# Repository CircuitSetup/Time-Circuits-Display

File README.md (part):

# Time Circuits Display

|  |

This [repository](https://github.com/CircuitSetup/Time-Circuits-Display) holds the most current firmware for CircuitSetup's wonderful [Time Circuits Display](https://circuitsetup.us/product/complete-time-circuits-display-kit/) ("TCD") kit, a reproduction of an iconic part of the Delorean Time Machine.

The kit is available [here](https://circuitsetup.us/product/complete-time-circuits-display-kit/). The metal version is very popular among Delorean owners who convert their vehicle into a Time Machine. A testament to its build quality and accuracy is further the fact that it is used in the **movie-based, official musicals on tour** (2024-2026), and that a sample is part of the experience in the **"OUTATIME" [Escape Room](https://www.universalorlando.com/web/en/us/things-to-do/entertainment/universals-great-movie-escape) in Orlando, Florida**. Namedropping aside, this TCD makes an excellent centerpiece of every movie props collection. It can be used stand-alone or in combination with several [peripherals](#peripherals), both in car and home setups.

[View the instructions for assembling your CircuitSetup TCD Kit](https://github.com/CircuitSetup/Time-Circuits-Display/wiki)

And don't be fooled by the looks, it got brains, too!

|  |
|:--:|
| Click to watch the video |

|  |
|:--:|
| Click to watch the video |

Features include

- Clock-related:
  - Time keeping for years 1-9999, accurately based on Julian and Gregorian [calendars](#calendar-system)
  - Support for time zones and automatic DST (Daylight Saving adjustment)
  - Time synchronization through Internet ([NTP&#10548;](https://en.wikipedia.org/wiki/Network_Time_Protocol)) or [GPS](#gps-receiver)
  - [World Clock mode](#world-clock-mode): Show current time in different time zones on *destination time* and/or *last time departed* displays
  - [Alarm function](#alarm): Daily alarms, with weekday selection as well as snooze and auto-snooze functions
  - [Count-down timer](#count-down-timer): Count down from up to 99 minutes
  - [Yearly/monthly reminder](#yearlymonthly-reminder): Get a yearly or monthly acoustic reminder
  - [Sound on the hour](#additional-custom-sounds)
  - Time can be [spoken out loud](#martys-time-announcement) by "Marty McFly"
- Movie-related:
  - Movie-accurate [Beep](#beep-on-the-second) sound every second (4 modes)
  - Movie-accurate [time travel](#time-travel) function
  - Configuration options to emulate nearly all variations of the TCD shown in the trilogy
  - ["Return from Time Travel"](#time-travel): Return to real present time easily
  - ["Time-cycling"](#time-cycling): Movie-accurate time travel times displayed in *destination time* and *last time departed* displays, and cycled in configurable interval
  - [Exhibition mode](#exhibition-mode): Show a fixed time in *Present Time* display instead of a running clock. Helpful for filming or museums.
- Network capabilities:
  - Advanced network-accessible [Config Portal](#the-config-portal) for setup (http://timecircuits.local)
  - [Wireless communication](#connecting-props-wirelessly-bttf-network-bttfn) with compatible props such as CircuitSetup's [Flux Capacitor](https://circuitsetup.us/product/flux-capacitor-light-sound-kit/) and [SID](https://circuitsetup.us/product/delorean-time-machine-status-indicator-display-sid/), as well as the [Dash Gauges](https://circuitsetup.us/product/delorean-time-machine-dash-gauge-control-board/), [VSR](https://vsr.out-a-ti.me) and modified [Futaba Remote Control](https://circuitsetup.us/product/futaba-remote-stanley-display-wireless-control-kit/), for synchronized Time Travel sequences, replaying movie scenes, mutual remote control, and more. No need for even more wires in your Delorean.
  - [Home Assistant](#home-assistant--mqtt) (MQTT) support for sending and displaying messages, remote controlling and more.
  - Easy [firmware updates](#firmware-installation--firmware-update) over-the-air. No need to send in stuff for firmware updates, it's the 2020s after all.
- [Night mode](#night-mode): Dim or switch off displays on schedule, manually or sensor-controlled. So you won't be blinded during night drives.
- Audio output through [line-out](#audio-output) for time travel sound, music and [user-added](#additional-custom-sounds) sound. Connect your TCD to your (car) stereo for high-quality stereo-sound. No more "time traveling" through a 2" speaker. (Requires Control Board 1.4.5 or later)
- [Music player](#the-music-player): Play your mp3 files located on SD card, through your (car) stereo if available. 
- [Keypad-controlled menu](#the-keypad-menu) for adjusting various settings and viewing status through the three displays
- Support for numerous [peripherals](#peripherals):
  - [Fake "power switch"](#fake-power-switch) (eg. a [TFC drive switch](https://tfc.out-a-ti.me))
  - [Speedometer](#speedometer) (eg. CircuitSetup's [speedo](https://circuitsetup.us/product/delorean-time-machine-speedometer-kit) with built-in GPS receiver)
  - [GPS receiver](#gps-receiver) for time synchronization and actual [speed](#gps-for-speed) to be displayed on speedo
  - [Rotary encoders](#rotary-encoder) for manual selection of speed to be displayed on speedo, and/or audio volume
  - External [Time Travel trigger](#external-time-travel-trigger), with optional delay
  - [Temperature/humidity sensor](#room-condition-mode-temperaturehumidity-sensor) for [Room Condition mode](#room-condition-mode-temperaturehumidity-sensor) [display temperature and humidity in *destination time* and *last time departed* displays] and for displaying temperature on speedo while idle
  - Multi-purpose output for signaling/controlling other props [connected by wire](#connecting-props-by-wire) (for example flux lights, third party props)
- &#128007; &#129370; &#129370; &#129370; &#129370; &#129370; &#129370; &#129370; &#129370; &#129370; &#129370; &#129370; &#129370;

>[The A10001986 repository](https://tcd.out-a%2dti.me) is the upstream source for CircuitSetup's firmware releases. The [A10001986 edition](https://tcd.out%2da-ti.me) uses a slightly different sound-pack compared to the CircuitSetup edition, otherwise there are no differences between A10001986 and CircuitSetup releases of the same version.

For information on updating the firmware of your TCD, see [here](#firmware-installation--firmware-update).

#### What's new in version 4.00?

- GPS speed logic change: "Display GPS speed" and "Provide GPS speed to BTTFN clients" Config Portal options are gone. User can now switch between _Evaluate GPS speed_ and _Do not evaluate GPS Speed_ on-the-fly through keypad command ```8```. This toggles between (a) displaying GPS speed on speedo as well as sending it to BTTFN clients, and (b) using a rotary encoder, displaying "0", temperature, or switching the speedo off, depending on hardware configuration and other option settings.
- If GPS does not have a fix, the speedo will display "-" permanently (and no longer switch to "0" after a while). To avoid this, issue keypad command ```8``` to switch away from GPS speed.
- The former GPS speed "Update rate" selector is now labeled "GPS speed" and got a "disabled" option item which allows categorically disable GPS speed (which should be done in case of a permanently stationary installation to avoid polling the GPS receiver unnecessarily frequently).
- GPS: Keypad commands ```950```/```951``` disable/enable the GPS fix indicator in the present time's year field. Defaults to on.
- GPS: Keypad menu now has an item that shows if a GPS receiver has been detected during boot.
- Fix for undetected GPS receivers on very long cables.
- Re-arrange WiFi Configuration page for a better user experience
- Remap "show weekday of current present time's date" keypad command to more handy ```3``` (instead of rather unintuitive 39).
- Keypad command ```1971159357```, when entered twice, resets all settings to factory defaults.
- Sound-pack uploads are done through the _top_ file selector on the "Update & Upload" page, and no longer through the bottom one. The bottom one is for custom mp3 file upload only.
- **Future firmware updates may only consist of one single file instead of "main firmware" plus "sound-pack". Firmware updates will require an SD card. In order to update to versions beyond 4.00, version 4.00 must be installed first.**

## Initial Configuration

**Some key features of your TCD require an SD card.** The first step is therefore to put a **good-quality** ("endurance", "industrial", "long life", ...) **and empty microSD card into the card slot** on the back of the keypad. The SD card must be inserted before powering up the TCD. It is not recognized if inserted while the TCD is running. Furthermore, do not remove the SD card while the TCD is powered.

>SD/SDHC/SDXC cards up to 32GB are supported. The card needs to be FAT32-formatted (not exFAT). Transcend, Sandisk Ultra and Industrial, Verbatim Premium and Samsung Pro Endurance SDHC cards usually work fine. Some SD cards might not be recognized due to off-specs initialization quirks. SDUC cards are not supported.

The second step is to establish access to the TCD's configuration website ("Config Portal") in order to configure your TCD:

- Power up the TCD and wait until it shows a time (which is probably wrong).
- Connect your computer or handheld device to the WiFi network "TCD-AP".
- Navigate your browser to http://timecircuits.local or http://192.168.4.1 to enter the Config Portal.

#### Time zone and Time

The next step is to set the time zone. If the time zone isn't properly configured, the TCD will show a wrong time and DST (daylight saving) will not be switched on/off correctly.

- Click on "Settings" on the Config Portal's main page,
- specify your [time zone](#-time-zone), and
- click "SAVE".

The TCD will reboot. Afterwards, please re-connect your computer/handheld to "TCD-AP" and re-enter the Config Portal as described above.

Setting actual time:
- If the TCD is going to be connected to a WiFi network with internet access as described below, it will receive time information through NTP (network time protocol). No user interaction is required.
- Otherwise please set your local time through the [keypad menu](#how-to-set-the-real-time-clock-rtc).

#### Sound-pack re-installation (Firmware 3.23 an onwards)

If your factory-fresh TCD came with firmware version 3.23 or later, but no SD card, the next step is to re-install the sound-pack. The reason for this is that the sound-pack does not entirely fit into the device's flash memory and parts of it need to be installed on your SD card. Please see [here](#sound-pack-installation) for instructions.

The firmware version is displayed in the footer of the Config Portal's main menu page.

#### WiFi Setup

The TCD knows two ways of WiFi operation: Either it creates its own WiFi network or it connects to a pre-existing WiFi network.

As long as the device is unconfigured, it creates a WiFi network of its own named "TCD-AP". This is called **"Access point mode"** or **"AP-mode"**. In this mode, other WiFi devices - such as other props or a computer - can connect to the TCD, but the TCD can't access the internet (and therefore not synchronize time through NTP). Also, [HA/MQTT](#home-assistant--mqtt) is not possible.

It is ok to leave the TCD in this mode if there is no WiFi network available.

<details>
<summary>More...</summary>

>Please do not leave computers/handhelds permanently connected to the TCD's AP. These devices might think they are connected to the internet and therefore hammer the TCD with DNS and HTTP requests which might lead to packet loss and disruptions.

>If you want your device to remain in AP-mode, please choose a suitable WiFi channel on the Config Portal's "WiFi Configuration" page. See [here](#-wifi-channel).

</details>

In a typical **home setup**, however, you might want to connect the TCD to your local WiFi network. This allows for for time synchronization (NTP) and [HA/MQTT](#home-assistant--mqtt):

To connect your TCD to your WiFi network, navigate to the Config Portal and click on "WiFi Configuration". The bare minimum is to select an WiFi network name (SSID) and a WiFi password.

<details>
<summary>More...</summary>
  
>If there are several access points (AP) with identical SSID nearby, the TCD will connect to the first one found which might not be the nearest/strongest. It is therefore recommended to select a specific AP by its BSSID (AP's MAC address). You can either manually find out your AP's BSSID and enter it or have it filled out automatically: Click "Scan for networks", then "Show all APs". If you click on an AP in the list, its BSSID will be copied into BSSID field in the form below. To see which AP is which, hover over the name to see its BSSID as a tooltip.

>The TCD requests an IP address via DHCP, unless you entered valid data in the fields for static IP addresses (IP, gateway, netmask, DNS). If the device is inaccessible as a result of incorrect static IPs, hold ```ENTER``` while powering it up until the white LED lights up; static IP data will be deleted and the device will return to using DHCP.
</details>

After saving the WiFi configuration settings, the TCD reboots and tries to connect to your selected WiFi network. If that fails, it will again start in access point mode.

If your TCD is **mounted in a car**, there is a special Car Mode that allows having a WiFi network configured (for administrative purposes and NTP time synchronization) and switching between AP-Mode and WiFi-connection through keypad commands. See [here](#car-mode) and [here](#car-setup---best-practice). So, despite using your TCD in a car, you can at this point configure a WiFi Connection, eg. to your cell phone's hotspot, and then put the TCD into Car Mode which reboots it into Access-Point mode.

After completing these steps, your TCD is ready for use; you can also continue configuring it to your personal preferences through the Config Portal.

## The Config Portal

The "Config Portal" is the TCD's configuration website. 

|  |
|:--:| 
| *The Config Portal's main page* |

It can be accessed as follows:

#### If TCD is in AP mode

- Connect your computer or handheld device to the WiFi network "TCD-AP".
- Navigate your browser to http://timecircuits.local or http://192.168.4.1 to enter the Config Portal.
- (For proper operation, please disconnect your computer or handheld from TCD-AP when you are done with configuring your TCD. These devices can cause high network traffic, resulting in severe performance penalties.)

#### If TCD is connected to WiFi network

- Connect your handheld/computer to the same WiFi network to which the TCD is connected, and
- navigate your browser to http://timecircuits.local

  <details>
  <summary>More...</summary>

  >Accessing the Config Portal through this address requires the operating system of your handheld/computer to support Bonjour/mDNS: Windows 10 version TH2     (1511) [other sources say 1703] and later, Android 13 and later; MacOS and iOS since the dawn of time.

  >If connecting to http://timecircuits.local fails due to a name resolution error, you need to find out the TCD's IP address: Hold ```ENTER``` on the TCD's keypad for 2 seconds, then repeatedly  press 8 until "NETWORK" is shown, then press ```5```. The TCD will show its current IP address. Then, on your handheld or computer, navigate to http://a.b.c.d (a.b.c.d being the IP address as shown on the display) in order to enter the Config Portal.
</details>

In the main menu, click on "Settings" or "Peripherals" to configure your TCD. 

|  |
|:--:| 
| *Click for full screenshot* |

A full reference of the Config Portal is [here](#appendix-a-the-config-portal).

## Basic Operation

*Present time* is a clock and normally shows actual local present time, as received from the network or set up through the [keypad menu](#how-to-set-the-real-time-clock-rtc).

*Destination time* and *Last time departed* are stale. These, by default, work like in the movie: Upon a time travel, *present time* becomes *last time departed*, and *destination time* becomes *present time*. Or in Doc's words: The red one tells you where you're going. The green one tells you where you are. The yellow one tells you where you were.

The keypad is for programming destination times like in the movies and for controlling the TCD through commands. "Keypad commands" are numerical codes to be typed on the digit keys followed by ```ENTER```. ```ENTER``` is the button right above the "Clear" badge.

<details>
<summary>"REPLACE BATTERY" displayed on boot?</summary>
If "REPLACE BATTERY" is shown upon boot, the onboard CR2032 battery is depleted and needs to be replaced. For technical reasons, "REPLACE BATTERY" will also show up the very first time you power-up the TCD *after* changing the battery. You can, of course, disregard that message at that point.
</details>

### Powering down the TCD

The TCD sometimes writes data to either the internal flash memory or the SD card. These write operations should not be interrupted by a power loss.

In general, it is safe to power-down the TCD after it has been [fake-powered-down](#fake-power-switch) or when it has been idle for 15 seconds. Try to avoid powering down the TCD
- when it is clearly busy (such as when copying or renaming audio files);
- within 15 seconds after changing the display mode (World Clock, Room condition, geolocation, …) or audio volume through a Rotary Encoder, 
- if [**_Make time travel persistent_**](#persistent--non-persistent-time-travels) is checked: in the first few seconds after a timetravel.

### Calendar system

The TCD firmware uses the [Julian Calendar&#10548;](https://en.wikipedia.org/wiki/Julian_calendar) from Jan 1, 1, until Sep 2, 1752, and for later dates the [Gregorian&#10548;](https://en.wikipedia.org/wiki/Gregorian_calendar) one. Sep 2, 1752, was the last day the Julian calendar was used in the ["First" British Empire&#10548;](https://en.wikipedia.org/wiki/British_Empire#%22First%22_British_Empire_(1707%E2%80%931783)) (Great Britain and its colonies, including eastern parts of North America, Canada). Other countries stopped using this calendar system way earlier; most of Europe, including Spain and its colonies worldwide, had switched in 1582 already.

Since the time machine was built in the USA, my guess is Doc would have picked 1752. (One might argue that California was a Spanish colony, but it only became that in 1769.)

So, what does this mean? First off, in the Julian calendar every 4th year is a leap year; in the Gregorian calendar there are some exceptions to this rule. As a result, the two calendars were drifting apart over time, and dates didn't match. As of 2023, the Julian calendar is 13 days ahead.

Secondly, and as a result of this drift, when countries switched from one to the other calendar system, days were skipped. In case of the switch in 1752, Sep 3 until Sep 13 were skipped, so after Sep 2 came Sep 14. For using the TCD this means that dates entered within that skipped period are corrected to Sep 14.

Neither the Gregorian nor the Julian Calendar know a "year 0"; 1AD followed after 1BC. Nevertheless, it is possible to travel to year 0. In good old Hollywood tradition, I won't let facts stand in the way of an authentic movie experience.

### Time-cycling

"Time cycling" is a decorative mode of operation in which the device cycles through a list of pre-programmed *destination* and *last time departed* times. These pre-programmed times match the dates/times of all time-travels that take place in the three movies.

Time-cycling is enabled by setting up a **_Time-cycling Interval_** in the Config Portal or the [keypad menu](#how-to-select-the-time-cycling-interval). The device will then cycle through named list every 5th, 10th, 15th, 30th or 60th minute. The option **_Animate time-cycling_** decides whether the times simply switch or the cycling event looks like someone entered a new destination date.

Triggering a time-travel pauses time-cycling for 30 minutes.

### World Clock mode

In World Clock (WC) mode, the red and yellow displays show not some stale times, but current time in other time zones. These time zones can be configured in Config Portal. At least one time zone (for either the red or yellow display) must be configured in order to use WC mode. Optionally, also names for cities/locations for these time zones can be entered in the Config Portal and shown [instead of the date or alternately](#world-clock-mode-1). Names can only contain letters a-z, numbers 0-9, space and minus. 

|  |
|:--:|
| Click to watch the video |

|  |
|:--:|
| *World Clock mode* |

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
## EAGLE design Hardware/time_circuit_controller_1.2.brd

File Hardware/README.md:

# PCB Revision History
## Control Board
v1.4.5 (8/1/24)
- Consolodated inputs/outputs into 8 pin screw connector
- Added label for TFC connections
- Added ground to audio line output screw connector
- Moved reset and io0 buttons to back of the board
- Added ability to switch between line out and speaker audio

v1.4 (7/1/24)
- Added dedicated audio line out
- Switched to original style TRW enter button
- Added on-board ESP32 module
- Added 3.3V power supply
- Added serial USB chip with ESD filtering
- Added micro-USB connector to back of board
- Moved RTC battery to rear of the PCB for ease of changing
- Changed volume pot to rear facing
- Moved micro-SD card to the rear of the board, and swtiched to a flip out holder
- 3d printed lens holder is now screwed to the PCB
- Changed Speedo and I2C to 2.54mm screw connectors
- Removed PCF2129AT and extra caps footprints
- Changed to TRW style mounting holes (3)

v1.3 (7/1/22)
- Added switch for lens LEDs
- Added header for TT In (GPIO 27)
- Added reverse polarity protection for power connectors
- Split resistors for keypad LEDs to make it so green LED can be brighter
- Added labels for PWR Trigger, TT Out, TT In, and Speedo

v1.2 (6/1/21)
- Fixed footprint for enter button
- Added 5.0V/3.3V level shifter, and ESD protection for I2C lines. This will prevent random glitches in I2C, and keep the ESP32 happy.
- Added footprint for PCF2129AT RTC in case DS3231 becomes unavailable or too expensive. Both should not be populated at the same time.
- Changed volume to connect to GPIO32 on ESP32 instead of amp GAIN_SLOT
- Updated schematic to include some notes

[OctoPart BOM](https://octopart.com/bom-tool/zCnlEeUa)

## Time Circuits Display
v1.31
- Made mounting holes slightly larger
- Moved some traces so they are not as close to pins

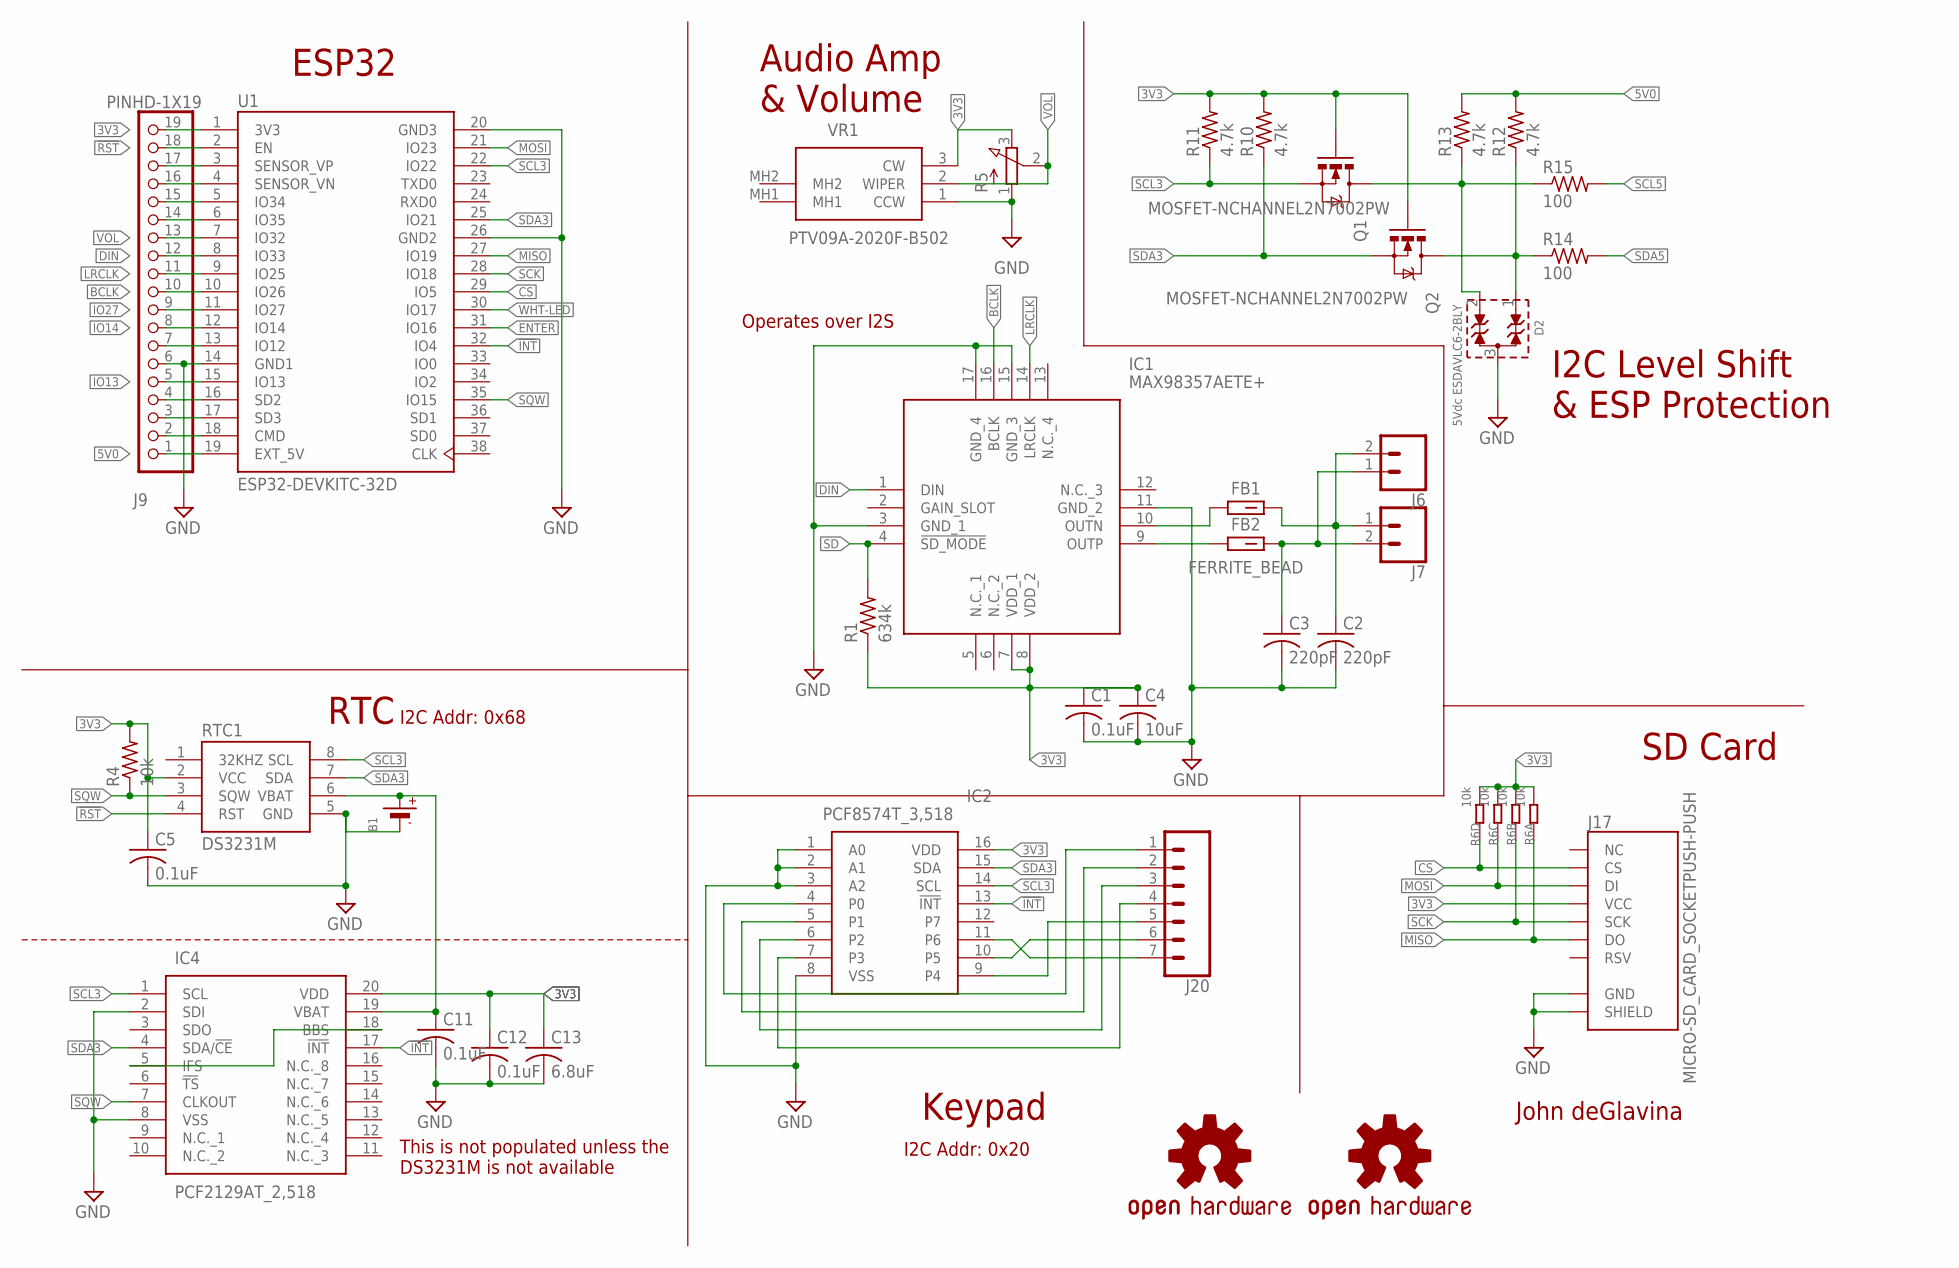
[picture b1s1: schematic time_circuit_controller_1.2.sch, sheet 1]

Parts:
B1: BATTERYCR2032_BAT-HLD-001; CR2032_SMT_BAT-HLD-001
C1, C5, C11, C12: 0.1uF; C0603
C2, C3: 220pF; C0603
C4: 10uF; C0603
C13: 6.8uF; C0603
D2: 5Vdc ESDAVLC6-2BLY; WE-TVS_SOT23-3L
FB1, FB2: FERRITE_BEAD; BEADC1608X95N
IC1: MAX98357AETE+; QFN50P300X300X80-17N
IC2: PCF8574T_3,518; SOIC127P1032X265-16N
IC4: PCF2129AT_2,518; SOIC127P1032X265-20N
J6: CONN_02-JST-2MM-SMT; JST-2-SMD
J7: CONN_02; 1X02
J9: PINHD-1X19; 1X19
J17: MICRO-SD_CARD_SOCKETPUSH-PUSH; MICRO-SD-SOCKET
J20: CONN_07LOCK; 1X07_LOCK
LOGO1, LOGO2: OSHW-LOGOL; OSHW-LOGO-L
Q1, Q2: MOSFET-NCHANNEL2N7002PW; SOT323
R1: 634k; R0603
R4: 10k; R0603
R5: 3RP/1610N
R6: 10k; RA1206-8
R10, R11, R12, R13: 4.7k; R0603
R14, R15: 100; R0603
RTC1: DS3231M; SO08
U1: ESP32-DEVKITC-32D; MODULE_ESP32-DEVKITC-32D
VR1: PTV09A-2020F-B502; PTV09A2020FB502

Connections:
3V3: C1.1, C4.1, C5.1, C12.1, C13.1, IC1.7 (VDD_1), IC1.8 (VDD_2), IC2.16 (VDD), IC4.20 (VDD), J9.19, J17.VCC, Q1.1 (G), Q2.1 (G), R1.1, R4.2, R5.3 (E), R6.1, R6.2 (1), R6.3 (1), R6.4 (1), R10.2, R11.2, RTC1.2 (VCC), U1.1 (3V3), VR1.3 (CW); also elsewhere on the board
5V0: J9.1, R12.2, R13.2, U1.19 (EXT_5V); also elsewhere on the board
!INT: IC2.13 (!INT), IC4.17 (!INT), U1.32 (IO4)
!RST: J9.18, RTC1.4 (RST), U1.2 (EN); also elsewhere on the board
AGND: B1.-, C1.2, C2.2, C3.2, C4.2, C5.2, C11.2, C12.2, C13.2, D2.3 (GND), IC1.3 (GND_1), IC1.11 (GND_2), IC1.15 (GND_3), IC1.17 (GND_4), IC2.1 (A0), IC2.2 (A1), IC2.3 (A2), IC2.8 (VSS), IC4.2 (SDI), IC4.8 (VSS), J9.6, J17.CD1 (SHIELD), J17.GND, R5.1 (A), RTC1.5 (GND), U1.14 (GND1), U1.20 (GND3), U1.26 (GND2), VR1.1 (CCW); also elsewhere on the board
BCLK: IC1.16 (BCLK), J9.10, U1.10 (IO26)
CS: J17.CS, R6.5 (2), U1.29 (IO5)
DIN: IC1.1 (DIN), J9.12, U1.8 (IO33)
ENTER: U1.31 (IO16); also elsewhere on the board
IO13: J9.5, U1.15 (IO13); also elsewhere on the board
IO14: J9.8, U1.12 (IO14); also elsewhere on the board
IO27: J9.9, U1.11 (IO27)
LRCLK: IC1.14 (LRCLK), J9.11, U1.9 (IO25)
MISO: J17.DO, R6.8 (2), U1.27 (IO19); also elsewhere on the board
MOSI: J17.DI, R6.6 (2), U1.21 (IO23); also elsewhere on the board
unnamed: IC2.11 (P6), J20.7
unnamed: FB1.1, IC1.10 (OUTN)
unnamed: B1.+$1 (+), B1.+$2 (+), C11.1, IC4.19 (VBAT), RTC1.6 (VBAT)
unnamed: IC2.4 (P0), J20.1
unnamed: IC2.9 (P4), J20.5
unnamed: J9.15, U1.5 (IO34)
unnamed: IC4.5 (IFS), IC4.18 (BBS)
unnamed: FB2.1, IC1.9 (OUTP)
unnamed: IC2.5 (P1), J20.2
unnamed: IC2.6 (P2), J20.3
unnamed: IC2.7 (P3), J20.4
unnamed: J9.14, U1.6 (IO35)
unnamed: IC2.10 (P5), J20.6
unnamed: J9.16, U1.4 (SENSOR_VN)
unnamed: J9.17, U1.3 (SENSOR_VP)
unnamed: J9.7, U1.13 (IO12)
unnamed: J9.4, U1.16 (SD2)
unnamed: J9.3, U1.17 (SD3)
unnamed: J9.2, U1.18 (CMD)
OUTN: C2.1, FB1.2, J6.2 (1), J7.1
OUTP: C3.1, FB2.2, J6.1 (2), J7.2
SCK: J17.SCLK (SCK), R6.7 (2), U1.28 (IO18); also elsewhere on the board
SCL3: IC2.14 (SCL), IC4.1 (SCL), Q1.2 (S), R11.1, RTC1.8 (SCL), U1.22 (IO22)
SCL5: R15.2; also elsewhere on the board
SD: IC1.4 (!SD_MODE), R1.2
SDA3: IC2.15 (SDA), IC4.4 (SDA/!CE), Q2.2 (S), R10.1, RTC1.7 (SDA), U1.25 (IO21)
SDA5: R14.2; also elsewhere on the board
SQW: IC4.7 (CLKOUT), R4.1, RTC1.3 (SQW), U1.35 (IO15)
VOL: J9.13, R5.2 (S), U1.7 (IO32), VR1.2 (WIPER)
WHT-LED: U1.30 (IO17); also elsewhere on the board
_SCL5: D2.2 (I/O2), Q1.3 (D), R13.1, R15.1
_SDA5: D2.1 (I/O1), Q2.3 (D), R12.1, R14.1

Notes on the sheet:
RTC
Keypad
SD Card
ESP32
I2C Level Shift & ESP Protection
Audio Amp & Volume
John deGlavina
This is not populated unless the DS3231M is not available
I2C Addr: 0x68
Operates over I2S
I2C Addr: 0x20

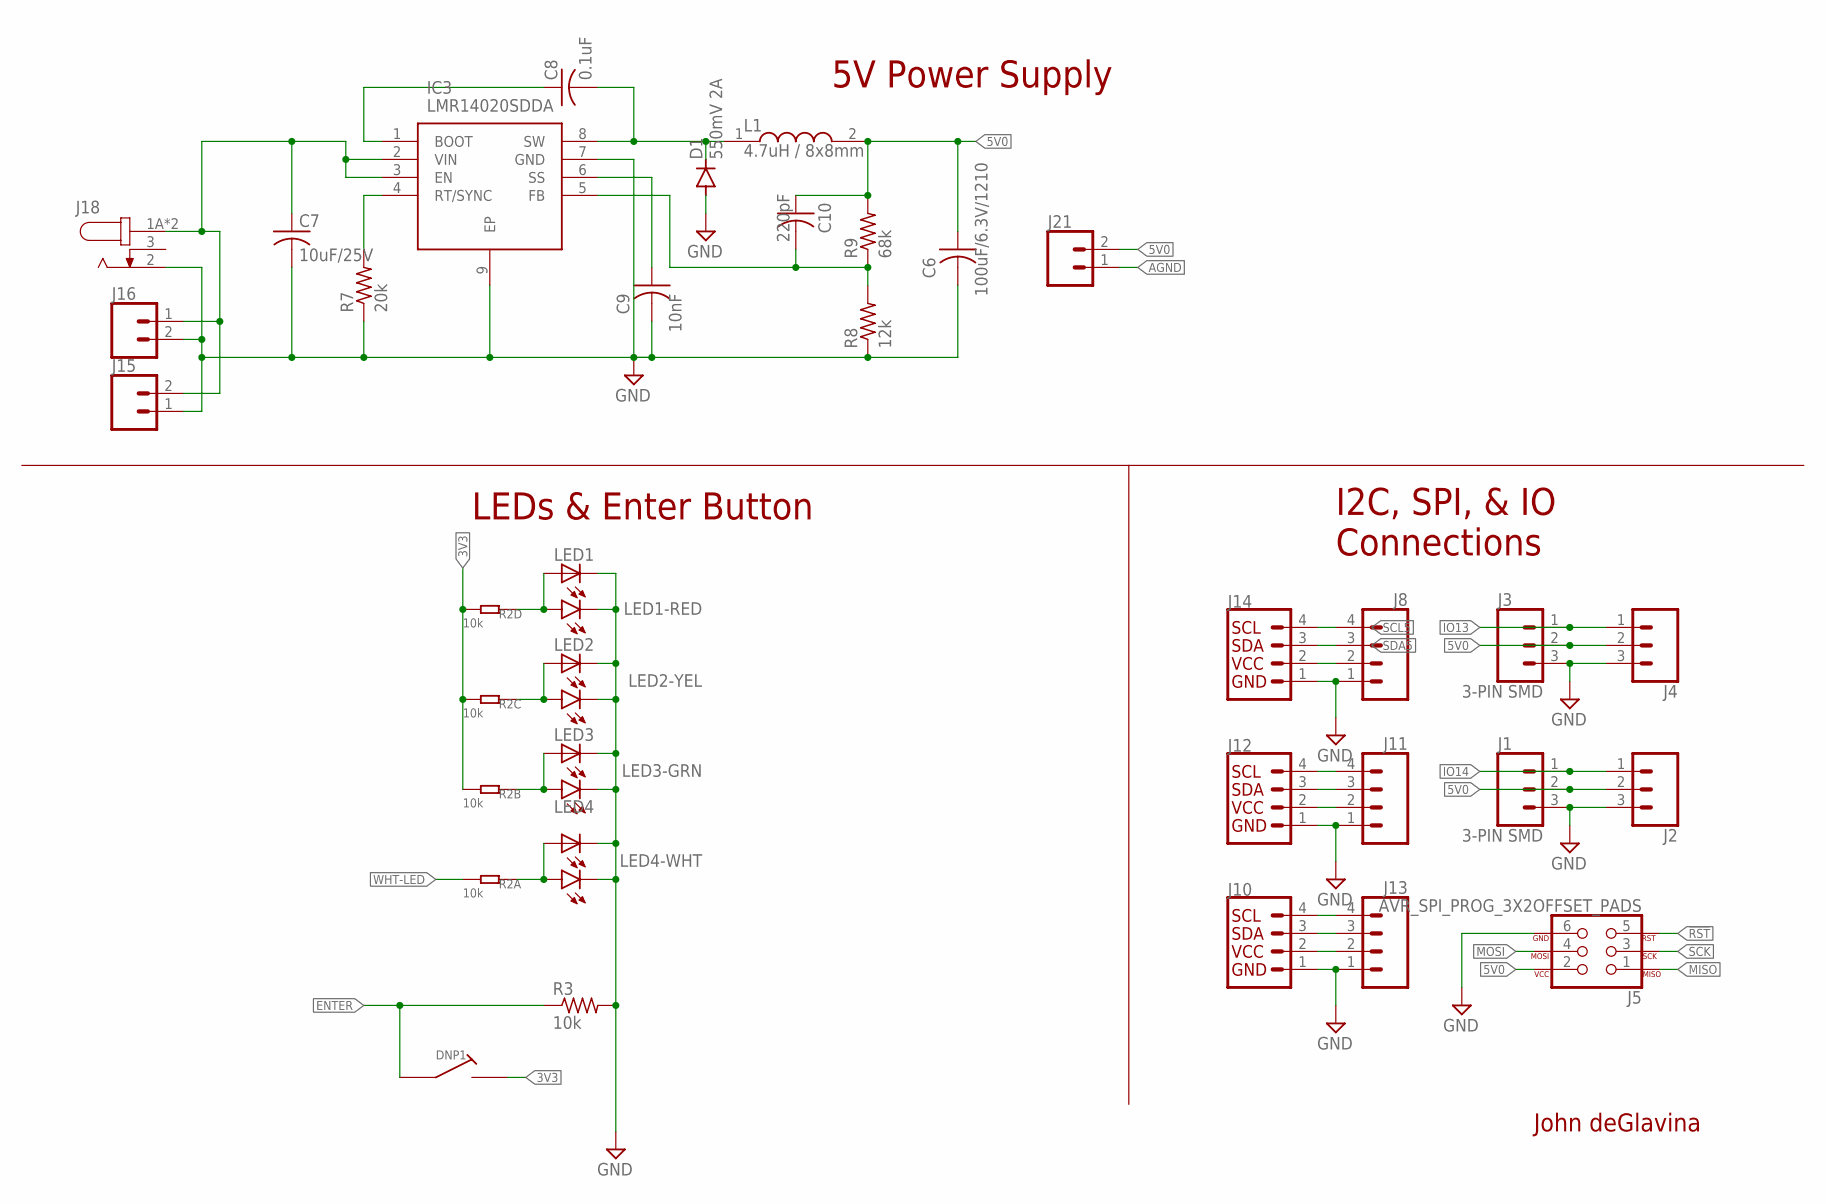
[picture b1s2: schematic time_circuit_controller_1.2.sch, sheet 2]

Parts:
C6: 100uF/6.3V/1210; C1210
C7: 10uF/25V; C0805
C8: 0.1uF; C0603
C9: 10nF; C0603
C10: 220pF; C0603
D1: 550mV 2A; DO214AC
DNP1: SWITCH-PINHEAD; PIN-1X2-3.5MM
IC3: LMR14020SDDA; SOIC127P600X170-9N
J1, J3: 3-PIN SMD; JST-3-SMD
J2, J4: CONN_03LOCK_LONGPADS; 1X03_LOCK_LONGPADS
J5: AVR_SPI_PROG_3X2OFFSET_PADS; 2X3_OFFSET
J8, J11, J13: CONN_04SMD_2.54; 1X04_5.5MM_STRAIGHT
J10, J12, J14: I2C_STANDARD; 1X04
J15, J21: CONN_023.5MM; SCREWTERMINAL-3.5MM-2
J16: CONN_02-JST-2MM-SMT; JST-2-SMD
J18: 9-12VAC; CUI_PJ-002AH-SMT-TR
L1: 4.7uH / 8x8mm; INDPM8082X300N
LED1, LED2, LED3, LED4: LEDCHIPLED_1206; CHIPLED_1206
LED1-RED, LED2-YEL, LED3-GRN, LED4-WHT: LED5MM
R2: 10k; RA1206-8
R3: 10k; R0603
R7: 20k; R0603
R8: 12k; R0603
R9: 68k; R0603

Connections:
3V3: DNP1.P$2 (2), R2.2 (1), R2.3 (1), R2.4 (1); also elsewhere on the board
5V0: C6.1, C10.1, J1.2, J2.2, J3.2, J4.2, J5.2, J8.2, J10.2, J11.2, J12.2, J13.2, J14.2, J21.2, L1.2, R9.2; also elsewhere on the board
!RST: J5.5; also elsewhere on the board
AGND: C6.2, C7.2, C9.2, D1.A, IC3.7 (GND), IC3.9 (EP), J1.3 (1), J2.3, J3.3 (1), J4.3, J5.6, J8.1, J10.1, J11.1, J12.1, J13.1, J14.1, J15.1, J16.2 (1), J18.2, J21.1, LED1.C, LED1-RED.K (C), LED2.C, LED2-YEL.K (C), LED3.C, LED3-GRN.K (C), LED4.C, LED4-WHT.K (C), R3.2, R7.1, R8.1; also elsewhere on the board
BOOT1: C8.1, IC3.1 (BOOT)
ENTER: DNP1.P$1 (1), R3.1; also elsewhere on the board
FB1: C10.2, IC3.5 (FB), R8.2, R9.1
IO13: J3.1 (3), J4.1; also elsewhere on the board
IO14: J1.1 (3), J2.1; also elsewhere on the board
MISO: J5.1; also elsewhere on the board
MOSI: J5.4; also elsewhere on the board
unnamed: LED1.A, LED1-RED.A, R2.5 (2)
unnamed: LED2.A, LED2-YEL.A, R2.6 (2)
unnamed: LED3.A, LED3-GRN.A, R2.7 (2)
unnamed: LED4.A, LED4-WHT.A, R2.8 (2)
RT1: IC3.4 (RT/SYNC), R7.2
SCK: J5.3; also elsewhere on the board
SCL5: J8.4, J10.4, J11.4, J12.4, J13.4, J14.4; also elsewhere on the board
SDA5: J8.3, J10.3, J11.3, J12.3, J13.3, J14.3; also elsewhere on the board
SS1: C9.1, IC3.6 (SS)
SW1: C8.2, D1.C, IC3.8 (SW), L1.1
VIN1: C7.1, IC3.2 (VIN), IC3.3 (EN), J15.2, J16.1 (2), J18.1A (1), J18.1B (1)
WHT-LED: R2.1; also elsewhere on the board

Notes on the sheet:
5V Power Supply
LEDs & Enter Button
I2C, SPI, & IO Connections
John deGlavina

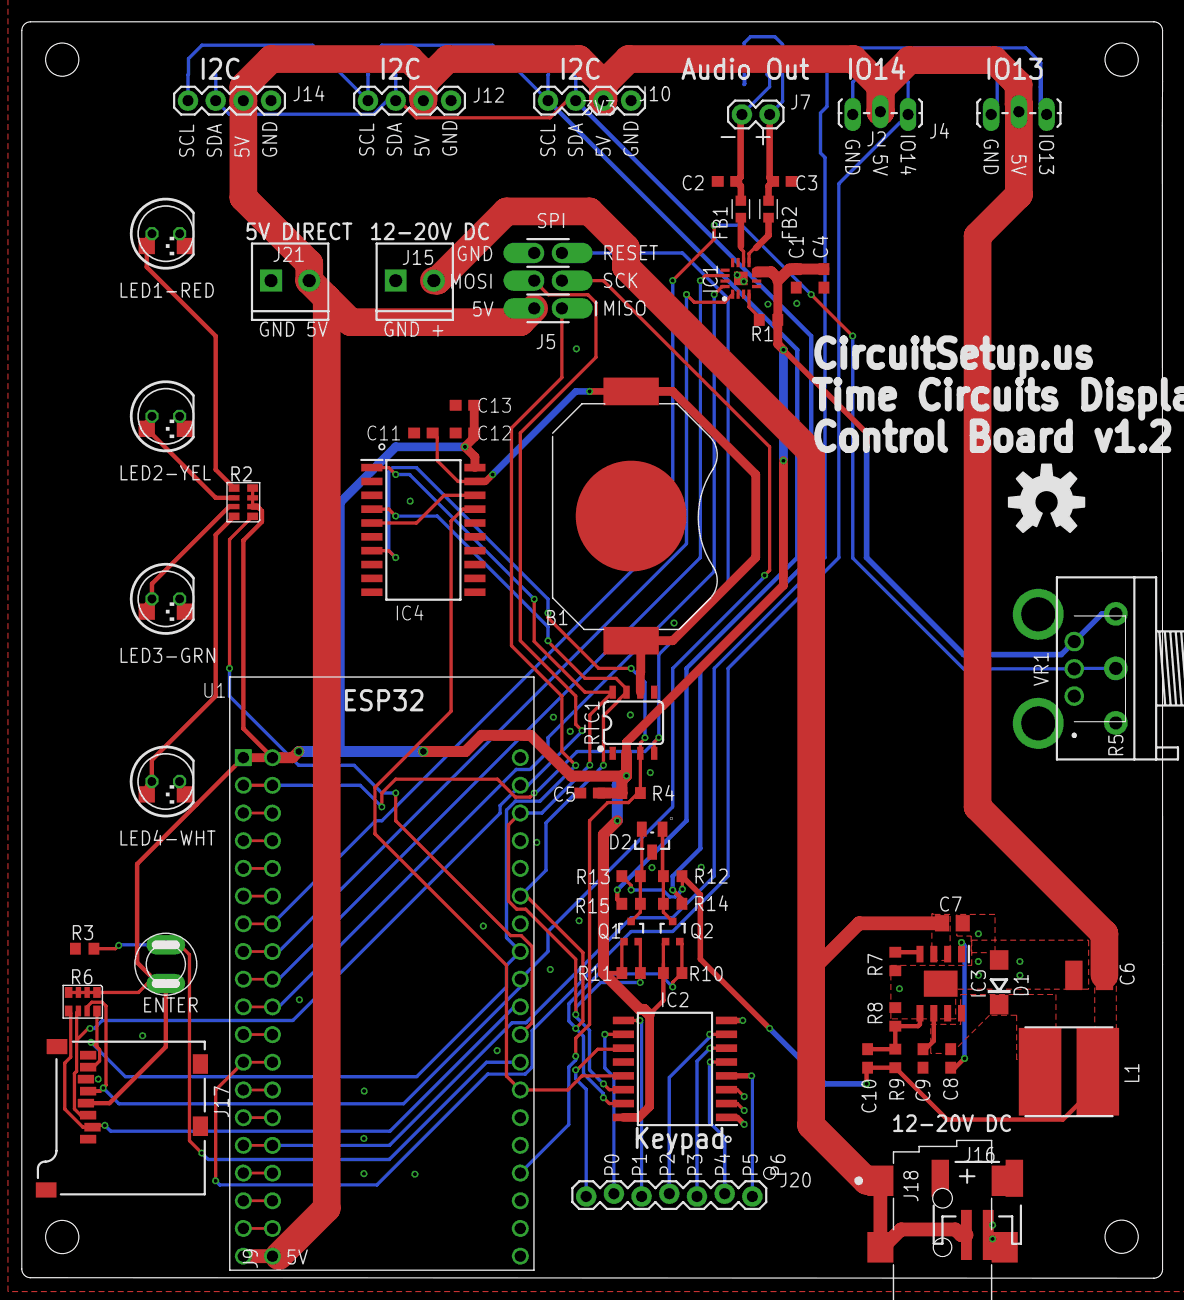
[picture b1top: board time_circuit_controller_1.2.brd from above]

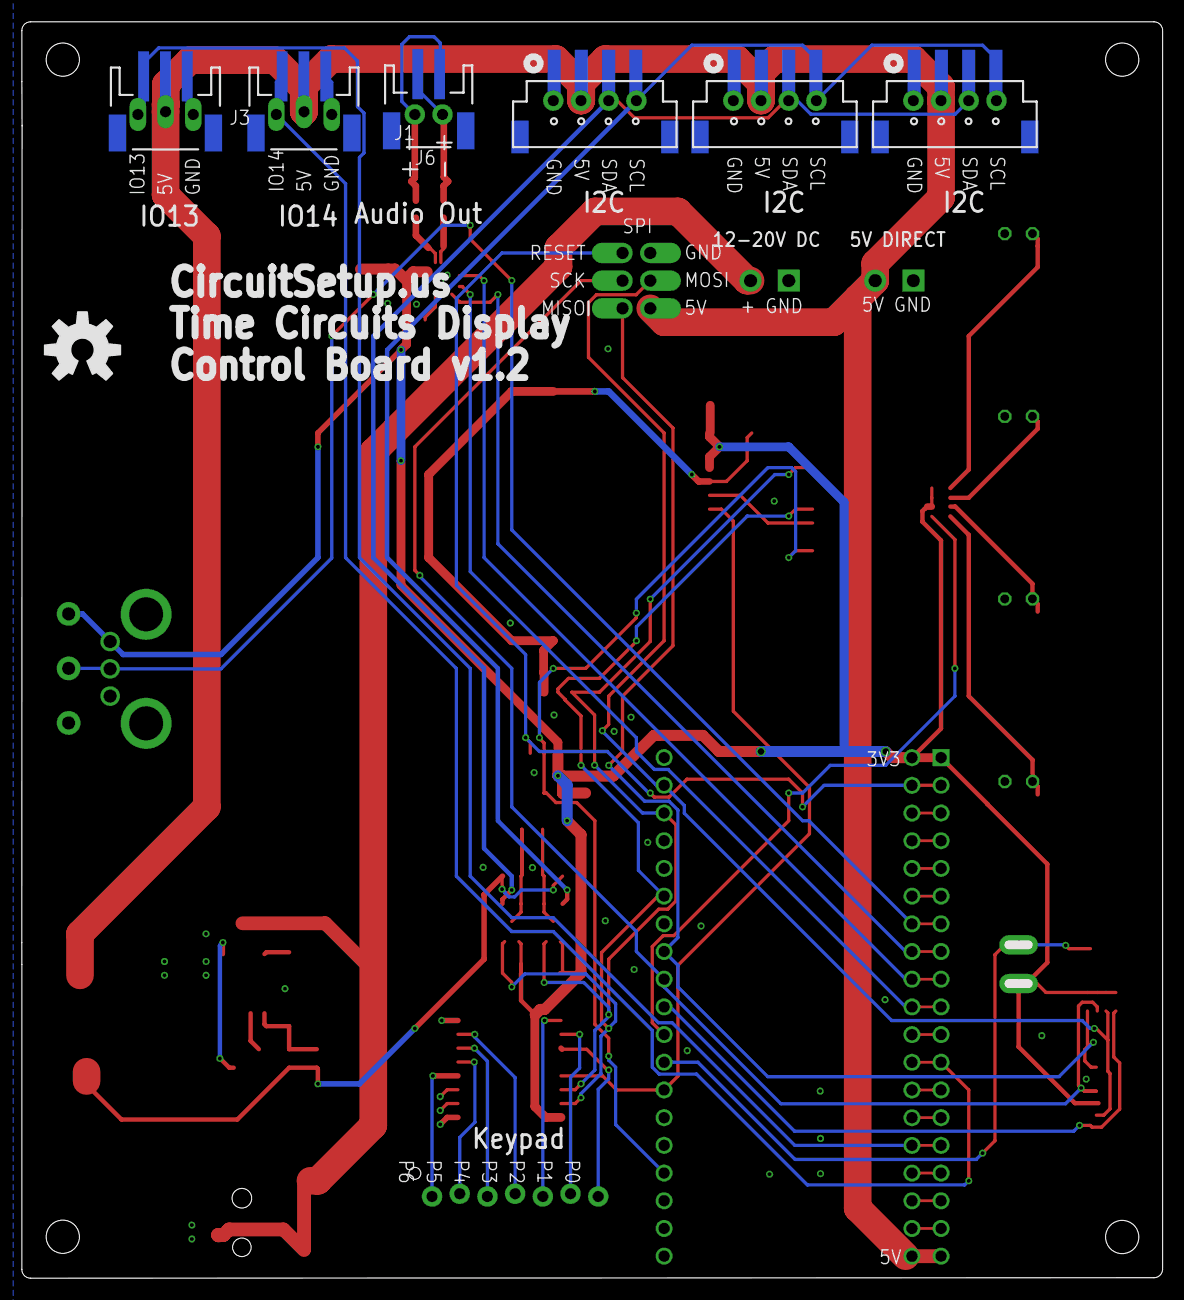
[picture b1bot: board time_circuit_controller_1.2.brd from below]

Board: 2 copper layers, 104.6 x 115.2 mm, 74 parts (7 on the bottom side), 57 nets.

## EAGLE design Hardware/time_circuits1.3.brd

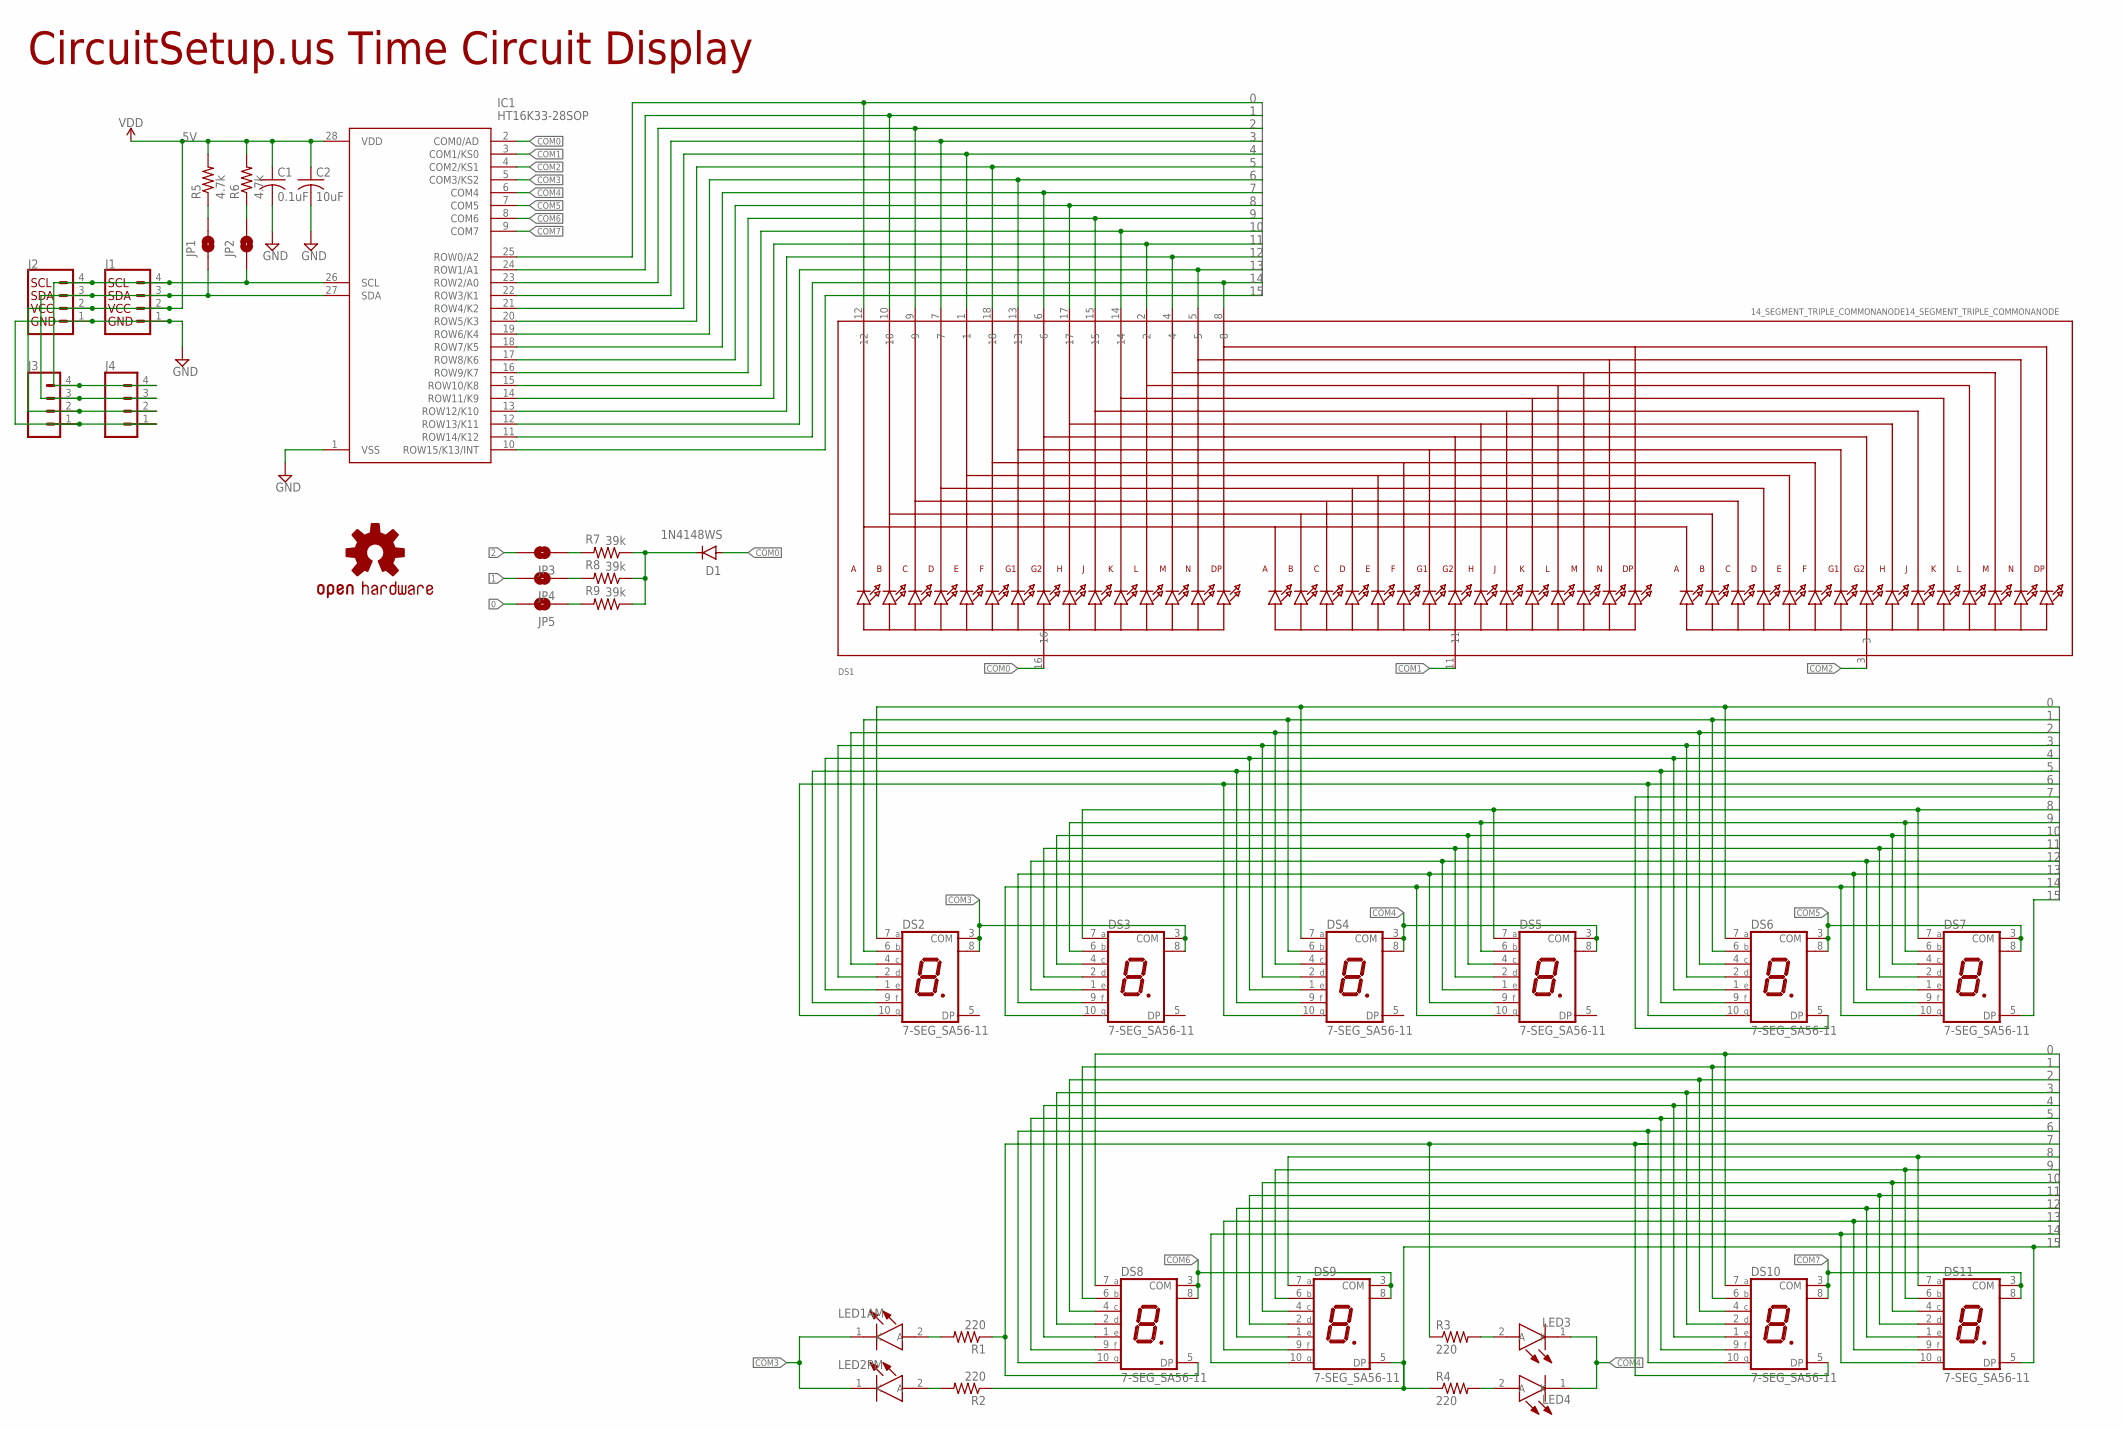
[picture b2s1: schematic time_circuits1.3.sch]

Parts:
C1: 0.1uF; C0603
C2: 10uF; C0603
D1: 1N4148WS; SOD-323
DS1: 14_SEGMENT_TRIPLE_COMMONANODE14_SEGMENT_TRIPLE_CO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; SEGMENT_TRIPLE_14
DS2, DS3, DS4, DS5, DS6, DS7, DS8, DS9, DS10, DS11: 7-SEG_SA56-11; SA56-11
IC1: HT16K33-28SOP; SOIC127P1031X264-28N
J1, J2: I2C_STANDARD; 1X04
J3, J4: CONN_04SMD_2.54; 1X04_5.5MM_STRAIGHT
JP1, JP2, JP3, JP4, JP5: JUMPER-SMT_2_NO_SILK; SMT-JUMPER_2_NO_SILK
LED1AM, LED2PM, LED3, LED4: WP132XGD
LOGO1: OSHW-LOGOL; OSHW-LOGO-L
R1, R2, R3, R4: 220; R0603
R5, R6: 4.7k; R0603
R7, R8, R9: 39k; R0603

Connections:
0: DS1.12, DS2.7 (A), DS4.7 (A), DS6.7 (A), DS8.7 (A), DS10.7 (A), IC1.25 (ROW0/A2), JP5.2
1: DS1.10, DS2.6 (B), DS4.6 (B), DS6.6 (B), DS8.6 (B), DS10.6 (B), IC1.24 (ROW1/A1), JP4.2
2: DS1.9, DS2.4 (C), DS4.4 (C), DS6.4 (C), DS8.4 (C), DS10.4 (C), IC1.23 (ROW2/A0), JP3.2
3: DS1.7, DS2.2 (D), DS4.2 (D), DS6.2 (D), DS8.2 (D), DS10.2 (D), IC1.22 (ROW3/K1)
4: DS1.1, DS2.1 (E), DS4.1 (E), DS6.1 (E), DS8.1 (E), DS10.1 (E), IC1.21 (ROW4/K2)
5: DS1.18, DS2.9 (F), DS4.9 (F), DS6.9 (F), DS8.9 (F), DS10.9 (F), IC1.20 (ROW5/K3)
5V: C1.1, C2.1, IC1.28 (VDD), J1.2, J2.2, J3.2, J4.2, R5.2, R6.2
6: DS1.13, DS2.10 (G), DS4.10 (G), DS6.10 (G), DS8.10 (G), DS10.10 (G), IC1.19 (ROW6/K4)
7: DS1.6, DS6.5 (DP), DS8.5 (DP), DS10.5 (DP), IC1.18 (ROW7/K5), R1.1, R3.1
8: DS1.17, DS3.7 (A), DS5.7 (A), DS7.7 (A), DS9.7 (A), DS11.7 (A), IC1.17 (ROW8/K6)
9: DS1.15, DS3.6 (B), DS5.6 (B), DS7.6 (B), DS9.6 (B), DS11.6 (B), IC1.16 (ROW9/K7)
10: DS1.14, DS3.4 (C), DS5.4 (C), DS7.4 (C), DS9.4 (C), DS11.4 (C), IC1.15 (ROW10/K8)
11: DS1.2, DS3.2 (D), DS5.2 (D), DS7.2 (D), DS9.2 (D), DS11.2 (D), IC1.14 (ROW11/K9)
12: DS1.4, DS3.1 (E), DS5.1 (E), DS7.1 (E), DS9.1 (E), DS11.1 (E), IC1.13 (ROW12/K10)
13: DS1.5, DS3.9 (F), DS5.9 (F), DS7.9 (F), DS9.9 (F), DS11.9 (F), IC1.12 (ROW13/K11)
14: DS1.8, DS3.10 (G), DS5.10 (G), DS7.10 (G), DS9.10 (G), DS11.10 (G), IC1.11 (ROW14/K12)
15: DS7.5 (DP), DS9.5 (DP), DS11.5 (DP), IC1.10 (ROW15/K13/INT), R2.1, R4.1
COM0: D1.A, DS1.16, IC1.2 (COM0/AD)
COM1: DS1.11, IC1.3 (COM1/KS0)
COM2: DS1.3, IC1.4 (COM2/KS1)
COM3: DS2.3 (COM), DS2.8 (COM), DS3.3 (COM), DS3.8 (COM), IC1.5 (COM3/KS2), LED1AM.1 (K), LED2PM.1 (K)
COM4: DS4.3 (COM), DS4.8 (COM), DS5.3 (COM), DS5.8 (COM), IC1.6 (COM4), LED3.1 (K), LED4.1 (K)
COM5: DS6.3 (COM), DS6.8 (COM), DS7.3 (COM), DS7.8 (COM), IC1.7 (COM5)
COM6: DS8.3 (COM), DS8.8 (COM), DS9.3 (COM), DS9.8 (COM), IC1.8 (COM6)
COM7: DS10.3 (COM), DS10.8 (COM), DS11.3 (COM), DS11.8 (COM), IC1.9 (COM7)
GND: C1.2, C2.2, IC1.1 (VSS), J1.1, J2.1, J3.1, J4.1
LED2: LED2PM.2 (A), R2.2
unnamed: JP1.2, R5.1
unnamed: JP2.2, R6.1
unnamed: JP3.1, R7.2
unnamed: JP4.1, R8.2
unnamed: JP5.1, R9.2
unnamed: D1.C, R7.1, R8.1, R9.1
unnamed: LED3.2 (A), R3.2
unnamed: LED4.2 (A), R4.2
unnamed: LED1AM.2 (A), R1.2
SCL: IC1.26 (SCL), J1.4, J2.4, J3.4, J4.4, JP2.1
SDA: IC1.27 (SDA), J1.3, J2.3, J3.3, J4.3, JP1.1

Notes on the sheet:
CircuitSetup.us Time Circuit Display

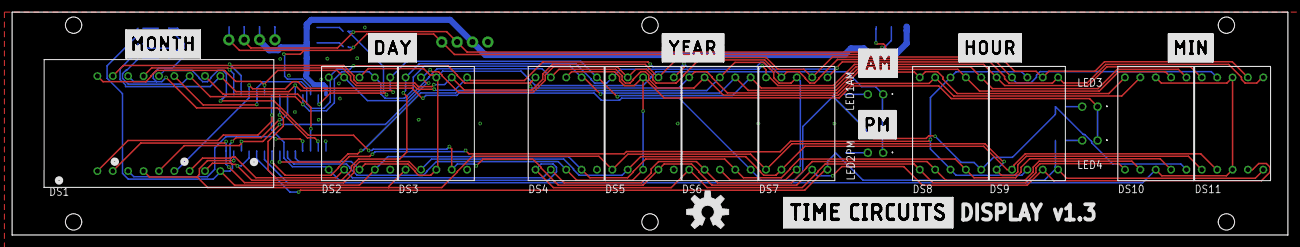
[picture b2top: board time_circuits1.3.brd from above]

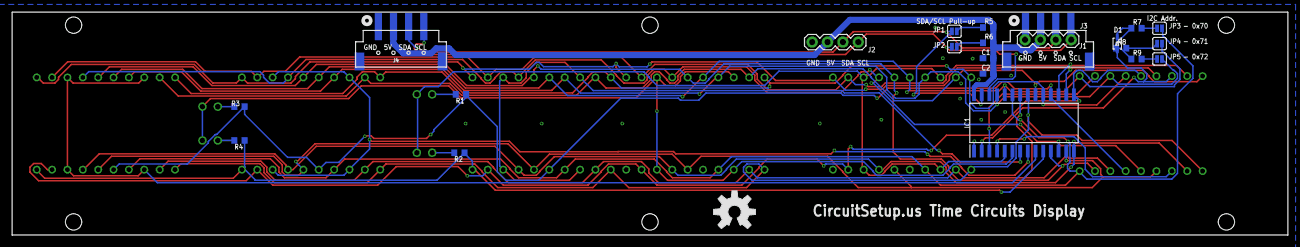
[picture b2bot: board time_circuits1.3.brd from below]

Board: 2 copper layers, 210.8 x 36.8 mm, 46 parts (23 on the bottom side), 38 nets.

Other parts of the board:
LOGO2: OSHW-LOGOL; OSHW-LOGO-L
U$1: MONTH
U$2: DAY
U$3: YEAR
U$4: HOUR
U$5: MIN
U$6: AM
U$7: PM

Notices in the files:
README.md:
_Text & images: (C) Thomas Winischhofer ("A10001986"). See LICENSE._ [Source](https://tcd.out%2da%2dti%2eme)
parts and their libraries:
SparkFun-Clocks: Licensing: Creative Commons ShareAlike 4.0 International - https://creativecommons.org/licenses/by-sa/4.0
Wurth_Elektronik_Passive_rev18f: Copyright: Würth Elektronik
